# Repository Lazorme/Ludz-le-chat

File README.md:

# KittyLudzinator Project

## Project Overview
The KittyLudzinator Project is focused on developing a playful autonomous robot equipped with an array of sensors including IMUs, Lidar, and motion detectors. It engages in a game of TAG, showcasing its ability to navigate and interact within its environment.

CHARBONENAU TOM

SERVAN Antoine

GILLES Baptiste

## Table of Contents
- [Project Overview](#project-overview)
- [Installation](#installation)
- [Usage](#usage)
- [Robot Strategy](#robot-strategy)
- [Doxygen](#Doxygen)
- [IMU](#IMU)
- [Directory Structure](#directory-structure)
- [License](#license)
- [Acknowledgments](#acknowledgments)
- [Contact Information](#contact-information)

## Installation
Refer to the [PCB](/PCB) directory for detailed component tables , PCB info and setup documentation. The software setup is managed through STM32CubeMX configurations (`Ludz_le_chat.ioc`), 

## Usage
The source code is located in [Code_Chat_V4.0](/Code_Chat_V4.0) with core functions in [Core](/Code_Chat_V4.0/Core).

The Lidar and motor drivers are in [drv_LIDAR](/Code_Chat_V4.0/drv_LIDAR) and [drv_Motor](/Code_Chat_V4.0/drv_Motor), respectively.

## Robot Strategy
Strategies for robot behavior in different modes are implemented as follows:

### Lidar Processing
Processes Lidar sensor data to track objects. Details are in the script [LIDAR_Receive_clusters.py](/LIDAR_Receive_clusters.py).

### Mouse Mode
The robot moves away from the tagger, inversely proportional to the angle of the tagger's approach.

### Hunter Mode
The 'it' robot aggressively seeks the nearest robot, adjusting its motor speed using a linear function.

### Edge Sensor
Edge detection prevents the robot from falling off ledges.

## Doxygen

## IMU
[IIMU](<Autres Codes/Code_IIM2070_SPI>) :This file includes instructions for operating the IIM2070 device, as detailed in the script code 'IIM2070_SPI

## Directory Structure
- [Code_Chat_V4.0](/Code_Chat_V4.0): Active robot code.
- [PCB](/PCB): Documentation, components and manufacturing file for PCB.
- [Doxygen](/Doxygen): Generated code documentation.
- [Autres Codes](/Autres_Codes): Previous versions and experimental code.

## License
The project is under the MIT License.

## Acknowledgments
Thanks to contributors and the open-source community.

## Contact Information
Contact the maintainer at .
[tom.charbonneau2001@gmail.com](mailto:tom.charbonneau2001@gmail.com) | [baptiste.gilles01@gmail.com](mailto:baptiste.gilles01@gmail.com)   |  [servan.antoine@gmail.com](mailto:servan.antoine@gmail.com)

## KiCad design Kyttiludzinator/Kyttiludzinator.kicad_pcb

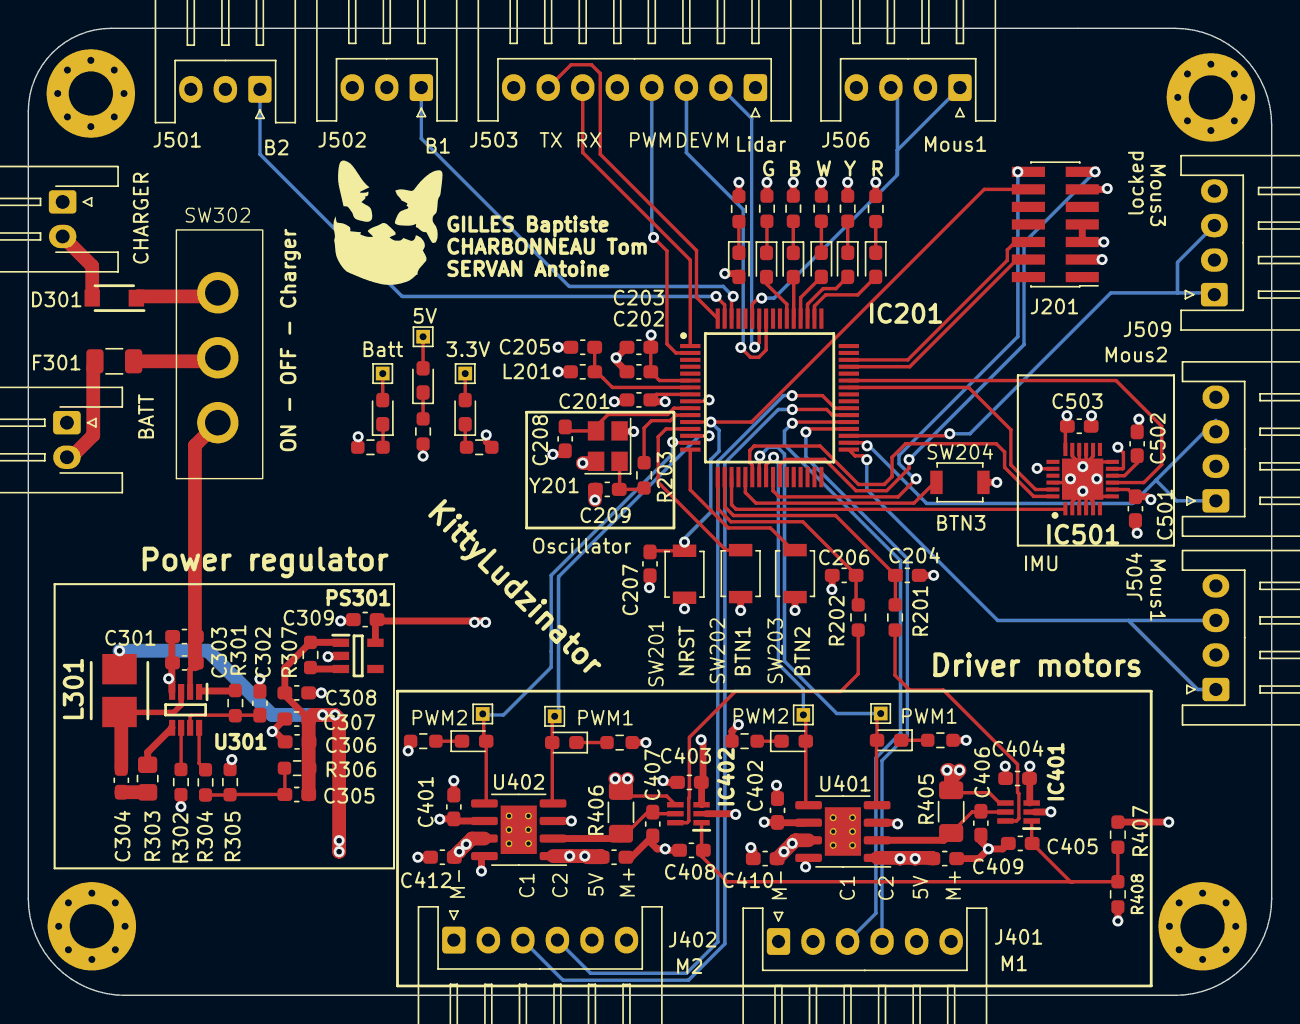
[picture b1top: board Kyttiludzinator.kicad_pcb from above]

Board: 4 copper layers, 90.0 x 70.0 mm, 104 parts (0 on the bottom side), 78 nets.

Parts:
Alim_batterie301: Conn_01x02; JST_XH_S2B-XH-A-1_1x02_P2.50mm_Horizontal
Alim_charger301: Conn_01x02; JST_XH_S2B-XH-A-1_1x02_P2.50mm_Horizontal
C201, C202, C205, C207, C403, C404, C405, C408, C502, C503: 100nF; C_0603_1608Metric_Pad1.08x0.95mm_HandSolder
C203: 4.7uF; C_0603_1608Metric_Pad1.08x0.95mm_HandSolder
C204, C206: 5pF; C_0603_1608Metric_Pad1.08x0.95mm_HandSolder
C208, C209: 10pF; C_0603_1608Metric_Pad1.08x0.95mm_HandSolder
C301, C306, C307: 22uF; C_0603_1608Metric_Pad1.08x0.95mm_HandSolder
C302, C303, C304: 0.1uF; C_0603_1608Metric_Pad1.08x0.95mm_HandSolder
C305: 15pF; C_0603_1608Metric_Pad1.08x0.95mm_HandSolder
C308, C309, C401, C402, C409, C410, C411, C412: 1uF; C_0603_1608Metric_Pad1.08x0.95mm_HandSolder
C406, C407: 10uF; C_0603_1608Metric_Pad1.08x0.95mm_HandSolder
C501: 10nF; C_0603_1608Metric_Pad1.08x0.95mm_HandSolder
D201: LED_ON; LED_0603_1608Metric_Pad1.05x0.95mm_HandSolder
D202, D401, D402, D403, D404, D404#2, D404#3, D404#4: RED; LED_0603_1608Metric_Pad1.05x0.95mm_HandSolder
D203: Yellow; LED_0603_1608Metric_Pad1.05x0.95mm_HandSolder
D204: BLUE; LED_0603_1608Metric_Pad1.05x0.95mm_HandSolder
D205: WHITE; LED_0603_1608Metric_Pad1.05x0.95mm_HandSolder
D206: GREEN; LED_0603_1608Metric_Pad1.05x0.95mm_HandSolder
D301: 1.5KExxA; SODFL3718X108N
F301: Polyfuse; Fuse_1206_3216Metric
IC201: STM32G070RBT6; QFP50P1200X1200X160-64N
IC401, IC402: NCS199A2RSQT2G; SOT65P210X110-6N
IC501: IIM-20670; IMU
J201: Conn_02x07_Odd_Even; PinHeader_2x07_P1.27mm_Vertical_SMD
J401, J402: Conn_01x06; JST_XH_S6B-XH-A_1x06_P2.50mm_Horizontal
J501, J502: Conn_01x03; JST_XH_S3B-XH-A_1x03_P2.50mm_Horizontal
J503: Conn_01x08; JST_XH_S8B-XH-A_1x08_P2.50mm_Horizontal
J504, J506, J509: Conn_01x04; JST_XH_S4B-XH-A_1x04_P2.50mm_Horizontal
L201: 6uH; L_0603_1608Metric_Pad1.05x0.95mm_HandSolder
L301: 4.7uH; INDPM4141X210N
PS301: MIC5317-3.3YM5-TR; SOT95P280X145-5N
R201, R202: 10k; R_0603_1608Metric_Pad0.98x0.95mm_HandSolder
R203: 10R; R_0603_1608Metric_Pad0.98x0.95mm_HandSolder
R204, R205, R206, R207, R208, R209: 3.3k; R_0603_1608Metric_Pad0.98x0.95mm_HandSolder
R301, R302, R307, R407, R408: 100k; R_0603_1608Metric_Pad0.98x0.95mm_HandSolder
R303: 20; R_0805_2012Metric_Pad1.20x1.40mm_HandSolder
R304: 16k; R_0603_1608Metric_Pad0.98x0.95mm_HandSolder
R305: 7.36k; R_0603_1608Metric_Pad0.98x0.95mm_HandSolder
R306: 40.2k; R_0603_1608Metric_Pad0.98x0.95mm_HandSolder
R401, R402, R403, R404#2: 390R; R_0603_1608Metric_Pad0.98x0.95mm_HandSolder
R404, R404#3, R404#4: 390; R_0603_1608Metric_Pad0.98x0.95mm_HandSolder
R405, R406: 0.015; R_1206_3216Metric_Pad1.30x1.75mm_HandSolder
REFe: MountingHole_3.2mm_M3_Pad_Via
SW201, SW202, SW203, SW204: SW_Push; SW_SPST_B3U-1000P
SW302: Switch; Switch-3
U301: MP1475DJ-LF-P; SOT65P280X100-8N
U401, U402: ZXBM5210-S; SOIC-8-1EP_3.9x4.9mm_P1.27mm_EP2.62x3.51mm_ThermalVias
Y201: 16MHz; Crystal_SMD_3225-4Pin_3.2x2.5mm
locked: Conn_01x04; JST_XH_S4B-XH-A_1x04_P2.50mm_Horizontal

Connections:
+3.3V: C201.1, C202.1, C203.1, C309.1, C403.1, C404.1, D201.2 (A), D404#3.2 (A), IC201.6 (VBAT), IC201.8 (VDD/VDDA), IC401.3 (VS), IC402.3 (VS), J201.3, J504.2, J504.4, J506.2, J506.4, J509.2, J509.4, L201.1, PS301.5 (VOUT), R404#4.2, R407.1, locked.2, locked.4
+5V: C305.2, C306.1, C307.1, C308.1, C401.1, C402.1, C501.2, C503.2, D404#4.2 (A), IC501.8 (VDDIO), IC501.11 (VDD), IC501.18 (RESETN), IC501.20 (VPP), J401.5, J402.5, J501.2, J502.2, J503.8, L301.2, PS301.1 (VIN), R306.2, R307.2, R404.1, U401.3 (VDD), U401.6 (VREF), U402.3 (VDD), U402.6 (VREF)
+BATT: C301.1, C303.1, D404.1 (K), D404.2 (A), IC402.4 (IN+), R302.2, R404#3.1, R405.1, R406.1, SW302.3 (C), U301.2 (IN)
/Drivers_moteurs/In_2-: C407.1, IC402.5 (IN-), R406.2, U402.2 (VM)
/Drivers_moteurs/M1_VM: C406.1, IC401.5 (IN-), R405.2, U401.2 (VM)
/Drivers_moteurs/Motor1+: C409.1, J401.6, U401.1 (OUT1)
/Drivers_moteurs/Motor1-: C410.1, J401.1, U401.7 (OUT2)
/Drivers_moteurs/Motor2+: C411.1, J402.6, U402.1 (OUT1)
/Drivers_moteurs/Motor2-: C412.1, J402.1, U402.7 (OUT2)
/Drivers_moteurs/REF: C405.1, C408.2, IC401.1 (REF), IC402.1 (REF), R407.2, R408.1
/STM32G070RBT6/BLUE: D204.2 (A), IC201.53 (PD3)
/STM32G070RBT6/BUTTON_1: IC201.13 (PC0), SW202.1
/STM32G070RBT6/BUTTON_2: IC201.16 (PC3), SW203.1
/STM32G070RBT6/BUTTON_3: IC201.21 (PA4), SW204.1
/STM32G070RBT6/GREEN: D206.2 (A), IC201.54 (PD4)
/STM32G070RBT6/NRST: C207.1, IC201.12 (NRST), J201.12, SW201.1
/STM32G070RBT6/OSC_IN: C208.1, IC201.10 (PF0-OSC_IN), Y201.3
/STM32G070RBT6/OSC_OUT: C209.2, IC201.11 (PF1-OSC_OUT), R203.1, R203.2, Y201.1
/STM32G070RBT6/RED: D202.2 (A), IC201.50 (PD0)
/STM32G070RBT6/RX: IC201.26 (PC5), J201.13
/STM32G070RBT6/SWCLK: IC201.46 (PA14-BOOT0), J201.6
/STM32G070RBT6/SWDIO: IC201.45 (PA13), J201.4
/STM32G070RBT6/TX: IC201.25 (PC4), J201.14
/STM32G070RBT6/VREF: C205.1, IC201.7 (VREF+), L201.2
/STM32G070RBT6/WHITE: D205.2 (A), IC201.52 (PD2)
/STM32G070RBT6/YELLOW: D203.2 (A), IC201.51 (PD1)
ADC_1: IC401.6 (OUT), R201.2
ADC_2: IC402.6 (OUT), R202.2
Bordure_1: IC201.62 (PB8), J502.1
Bordure_2: IC201.63 (PB9), J501.1
Codeur1_PH1: IC201.36 (PA8), J401.4
Codeur1_PH2: IC201.37 (PA9), J401.3
Codeur2_PH1: IC201.38 (PC6), J402.3
Codeur2_PH2: IC201.39 (PC7), J402.4
GND: Alim_batterie301.1, Alim_charger301.1, C201.2, C202.2, C203.2, C204.1, C205.2, C206.1, C207.2, C208.2, C209.1, C301.2, C302.1, C303.2, C306.2, C307.2, C308.2, C309.2, C401.2, C402.2, C403.2, C404.2, C405.2, C406.2, C407.2, C408.1, C409.2, C410.2, C411.2, C412.2, C501.1, C502.1, C503.1, IC201.9 (VSS/VSSA), IC401.2 (GND), IC402.2 (GND), IC501.2 (GND_1), IC501.3 (GND_2), IC501.4 (GND_3), IC501.5 (GND_4), IC501.7 (GND_5), IC501.12 (ODR), IC501.14 (GND_6), IC501.15 (GND_7), IC501.16 (GND_8), IC501.17 (GND_9), IC501.22 (GND_10), IC501.25 (THERMAL_PAD), J201.5, J201.7, J201.11, J401.2, J402.2, J501.3, J502.3, J503.5, PS301.2 (GND), R204.2, R205.2, R206.2, R207.2, R208.2, R209.2, R305.1, R401.2, R402.2, R403.2, R404.2, R404#2.2, R404#3.2, R404#4.1, R408.2, REFe.1, SW201.2, SW202.2, SW203.2, SW204.2, U301.4 (GND), U401.8 (GND), U402.8 (GND), Y201.2, Y201.4
LIDAR_DEV: IC201.57 (PB3), J503.3
LIDAR_M: IC201.58 (PB4), J503.2
LIDAR_PWM: IC201.2 (PC12), J503.4
LIDAR_RX: IC201.1 (PC11), J503.6
LIDAR_TX: IC201.64 (PC10), J503.7
Moustache_1: IC201.33 (PB13), J504.1, J504.3
Moustache_2: IC201.34 (PB14), J509.1, J509.3
Moustache_3: IC201.35 (PB15), locked.1, locked.3
Moustache_4: IC201.59 (PB5), J506.1, J506.3
unnamed: Alim_batterie301.2, F301.1
unnamed: Alim_charger301.2, D301.2 (A2)
unnamed: C304.2, R303.2
unnamed: C305.1, R304.2, R305.2, R306.1
unnamed: D201.1 (K), R204.1
unnamed: D202.1 (K), R205.1
unnamed: D203.1 (K), R206.1
unnamed: D204.1 (K), R207.1
unnamed: D205.1 (K), R208.1
unnamed: D206.1 (K), R209.1
unnamed: D301.1 (A1), SW302.1 (A)
unnamed: D401.1 (K), R401.1
unnamed: D402.1 (K), R402.1
unnamed: D403.1 (K), R403.1
unnamed: D404#2.1 (K), R404#2.1
unnamed: C206.2, IC201.17 (PA0), R202.1
unnamed: C204.2, IC201.18 (PA1), R201.1
unnamed: C502.2, IC501.10 (REGOUT)
unnamed: PS301.3 (EN), R307.1
unnamed: F301.2, SW302.2 (B)
unnamed: R303.1, U301.5 (BST)
unnamed: R302.1, U301.6 (EN/SYNC)
unnamed: R304.1, U301.8 (FB)
unnamed: R301.1, U301.1 (PG)
unnamed: C304.1, L301.1, U301.3 (SW)
unnamed: C302.2, R301.2, U301.7 (VCC)
PWM_MOT1_CH1: D401.2 (A), IC201.23 (PA6), U401.4 (FWD)
PWM_MOT1_CH2: D402.2 (A), IC201.24 (PA7), U401.5 (REV)
PWM_MOT2_CH1: D403.2 (A), IC201.14 (PC1), U402.4 (FWD)
PWM_MOT2_CH2: D404#2.2 (A), IC201.15 (PC2), U402.5 (REV)
SPI1_CS: IC201.42 (PA10), IC501.23 (NCS)
SPI1_MISO: IC201.43 (PA11_[PA9]), IC501.9 (MISO)
SPI1_MOSI: IC201.19 (PA2), IC501.1 (MOSI)
SPI1_SCK: IC201.22 (PA5), IC501.24 (SCLK)

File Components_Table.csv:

"Reference,""Value"",""Footprint"",""Datasheet"",""Height"",""Manufacturer_Name"",""Manufacturer_Part_Number"",""Mouser Part Number"",""Mouser Price/Stock"",""Qty"""
"Alim_batterie301,""Conn_01x02"",""Connector_JST:JST_XH_B2B-XH-A_1x02_P2.50mm_Vertical"",""~"","""","""","""","""","""",""1"""
"Alim_charger301,""Conn_01x02"",""Connector_JST:JST_XH_B2B-XH-A_1x02_P2.50mm_Vertical"",""~"","""","""","""","""","""",""1"""
"C201, C202, C205, C207, C403-C405, C502, C503,""100nF"",""Capacitor_SMD:C_0603_1608Metric_Pad1.08x0.95mm_HandSolder"",""~"","""","""","""","""","""",""9"""
"C203,""4.7uF"",""Capacitor_SMD:C_0603_1608Metric_Pad1.08x0.95mm_HandSolder"",""~"","""","""","""","""","""",""1"""
"C204, C206,""5pF"",""Capacitor_SMD:C_0603_1608Metric_Pad1.08x0.95mm_HandSolder"",""~"","""","""","""","""","""",""2"""
"C208, C209,""10pF"",""Capacitor_SMD:C_0603_1608Metric_Pad1.08x0.95mm_HandSolder"",""~"","""","""","""","""","""",""2"""
"C301, C306, C307,""22uF"",""Capacitor_SMD:C_0603_1608Metric_Pad1.08x0.95mm_HandSolder"",""~"","""","""","""","""","""",""3"""
"C302-C304,""0.1uF"",""Capacitor_SMD:C_0603_1608Metric_Pad1.08x0.95mm_HandSolder"",""~"","""","""","""","""","""",""3"""
"C305,""15pF"",""Capacitor_SMD:C_0603_1608Metric_Pad1.08x0.95mm_HandSolder"",""~"","""","""","""","""","""",""1"""
"C308, C309, C401, C402,""1uF"",""Capacitor_SMD:C_0603_1608Metric_Pad1.08x0.95mm_HandSolder"",""~"","""","""","""","""","""",""4"""
"C406, C407,""10uF"",""Capacitor_SMD:C_0603_1608Metric"",""~"","""","""","""","""","""",""2"""
"C501,""10nF"",""Capacitor_SMD:C_0603_1608Metric_Pad1.08x0.95mm_HandSolder"",""~"","""","""","""","""","""",""1"""
"D201,""LED_ON"",""LED_SMD:LED_0603_1608Metric_Pad1.05x0.95mm_HandSolder"",""~"","""","""","""","""","""",""1"""
"D202, D401-D404,""RED"",""LED_SMD:LED_0603_1608Metric_Pad1.05x0.95mm_HandSolder"",""~"","""","""","""","""","""",""5"""
"D203,""Yellow"",""LED_SMD:LED_0603_1608Metric_Pad1.05x0.95mm_HandSolder"",""~"","""","""","""","""","""",""1"""
"D204,""BLUE"",""LED_SMD:LED_0603_1608Metric_Pad1.05x0.95mm_HandSolder"",""~"","""","""","""","""","""",""1"""
"D205,""WHITE"",""LED_SMD:LED_0603_1608Metric_Pad1.05x0.95mm_HandSolder"",""~"","""","""","""","""","""",""1"""
"D206,""GREEN"",""LED_SMD:LED_0603_1608Metric_Pad1.05x0.95mm_HandSolder"",""~"","""","""","""","""","""",""1"""
"D301,""1.5KExxA"",""Library:SODFL3718X108N"",""https://www.vishay.com/docs/88301/15ke.pdf"","""",""Vishay"","""","" 78-SS2FN6HM3/H "",""https://www.mouser.fr/ProductDetail/Vishay-General-Semicondu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"",""1"""
"F301,""Polyfuse"",""Fuse:Fuse_1206_3216Metric"",""~https://www.mouser.fr/datasheet/2/54/bourns_01242019_MF-NSML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"",""1206"",""Boums"","""","" 652-MF-NSML150/12-2 "",""https://www.mouser.fr/ProductDetail/Bourns/MF-NSML150-12-2?q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"",""1"""
"IC201,""STM32G070RBT6"",""Library:QFP50P1200X1200X160-64N"",""https://componentsearchengine.com/Datasheets/1/STM32G070RBT6.pdf"",""1.6"",""STMicroelectronics"",""STM32G070RBT6 "",""511-STM32G070RBT6"",""https://www.mouser.co.uk/ProductDetail/STMicroelectronics/ST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"",""1"""
"IC401, IC402,""NCS199A2RSQT2G"",""Library:SOT65P210X110-6N"",""http://www.onsemi.com/pub/Collateral/NCS199A1R-D.PDF"",""1.1"",""onsemi"",""NCS199A2RSQT2G"",""863-NCS199A2RSQT2G"",""https://www.mouser.co.uk/ProductDetail/onsemi/NCS199A2RSQT2G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"",""2"""
"IC501,""IIM-20670"",""Library:IMU"",""https://invensense.tdk.com/download-pdf/iim-20670-product-brief/"",""1.15"",""TDK"",""IIM-20670"","" 410-IIM-20670 "",""https://www.mouser.fr/ProductDetail/TDK-InvenSense/IIM-20670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"",""1"""
"J201,""Conn_02x07_Odd_Even"",""Connector_PinHeader_2.54mm:PinHeader_2x07_P2.54mm_Vertical"",""~"","""","""","""","""","""",""1"""
"J401, J402,""Conn_01x06"",""Connector_JST:JST_XH_B6B-XH-A_1x06_P2.50mm_Vertical"",""~"","""","""","""","""","""",""2"""
"J501, J502, J504-J507,""Conn_01x03"",""Connector_JST:JST_XH_B3B-XH-A_1x03_P2.50mm_Vertical"",""~"","""","""","""","""","""",""6"""
"J503,""Conn_01x08"",""Connector_JST:JST_XH_B8B-XH-A_1x08_P2.50mm_Vertical"",""~"","""","""","""","""","""",""1"""
"L201,""6uH"",""Inductor_SMD:L_0603_1608Metric"",""~"","""","""","""","""","""",""1"""
"L301,""4.7uH"",""Library:INDPM4141X210N"",""https://www.we-online.com/components/products/datasheet/7443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"","""",""Wurth"",""74438356047HT "","" 710-74438356047HT "",""https://www.mouser.fr/ProductDetail/Wurth-Elektronik/7443835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"",""1"""
"PS301,""MIC5317-3.3YM5-TR"",""Library:SOT95P280X145-5N"",""http://ww1.microchip.com/downloads/en/devicedoc/mic5317.pdf"",""1.45"",""Microchip"",""MIC5317-3.3YM5-TR"",""998-MIC5317-3.3YM5TR"",""https://www.mouser.co.uk/ProductDetail/Microchip-Technology/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"",""1"""
"R201, R202,""10k"",""Resistor_SMD:R_0603_1608Metric_Pad0.98x0.95mm_HandSolder"",""~"",""0603"","""","""","""","""",""2"""
"R203,""10R"",""Resistor_SMD:R_0603_1608Metric_Pad0.98x0.95mm_HandSolder"",""~"",""0603"","""","""","""","""",""1"""
"R204-R209,""3.3k"",""Resistor_SMD:R_0603_1608Metric_Pad0.98x0.95mm_HandSolder"",""~"",""0603"","""","""","""","""",""6"""
"R301, R302, R407, R408,""100k"",""Resistor_SMD:R_0603_1608Metric_Pad0.98x0.95mm_HandSolder"",""~"",""0603"","""","""","""","""",""4"""
"R303,""20"",""Resistor_SMD:R_0805_2012Metric_Pad1.20x1.40mm_HandSolder"",""~"",""0805"","""","""","""","""",""1"""
"R304,""16k"",""Resistor_SMD:R_0603_1608Metric_Pad0.98x0.95mm_HandSolder"",""~"",""0603"","""","""","""","""",""1"""
"R305,""7.36k"",""Resistor_SMD:R_0603_1608Metric_Pad0.98x0.95mm_HandSolder"",""~"",""0603"","""","""","""","""",""1"""
"R306,""40.2k"",""Resistor_SMD:R_0603_1608Metric_Pad0.98x0.95mm_HandSolder"",""~"",""0603"","""","""","""","""",""1"""
"R401-R404,""390R"",""Resistor_SMD:R_0603_1608Metric_Pad0.98x0.95mm_HandSolder"",""~"",""0603"","""","""","""","""",""4"""
"R405, R406,""0.015"",""Resistor_SMD:R_1206_3216Metric_Pad1.30x1.75mm_HandSolder"",""~"",""0603"","""","""","""","""",""2"""
"SW201-SW204,""SW_Push"",""Button_Switch_SMD:SW_SPST_B3U-1000P"",""~"",""1206"","""","""","""","""",""4"""
"SW302,""Switch"",""Library:Switch-3"",""https://www.we-online.com/en/components/products/WS-TOTV_635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"","""",""Wurth"",""WS-TOTV Ø 6.35mm"",""1333652"","""",""1"""
"U301,""MP1475DJ-LF-P"",""Library:SOT65P280X100-8N"",""https://www.mouser.fr/datasheet/2/277/MP1475-2945395.pdf"","""","" Monolithic Power Systems (MPS)"",""MP1475DJ"","" 946-MP1475DJLFP "",""https://www.mouser.fr/ProductDetail/Monolithic-Power-Systems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"",""1"""
"U401, U402,""ZXBM5210-S"",""Library:SOIC127P600X175-8N"",""https://www.diodes.com/assets/Datasheets/ZXBM5210.pdf"","""","""","""","" 621-ZXBM5210-SP-13 "",""https://www.mouser.fr/ProductDetail/Diodes-Incorporated/ZXBM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"",""2"""
"Y201,""16MHz"",""Crystal:Crystal_SMD_3225-4Pin_3.2x2.5mm"",""https://www.farnell.com/datasheets/3820205.pdf"","""",""ZXBM5210-SP-13"",""Diodes Incorporated "",""2853935"","""",""1"""

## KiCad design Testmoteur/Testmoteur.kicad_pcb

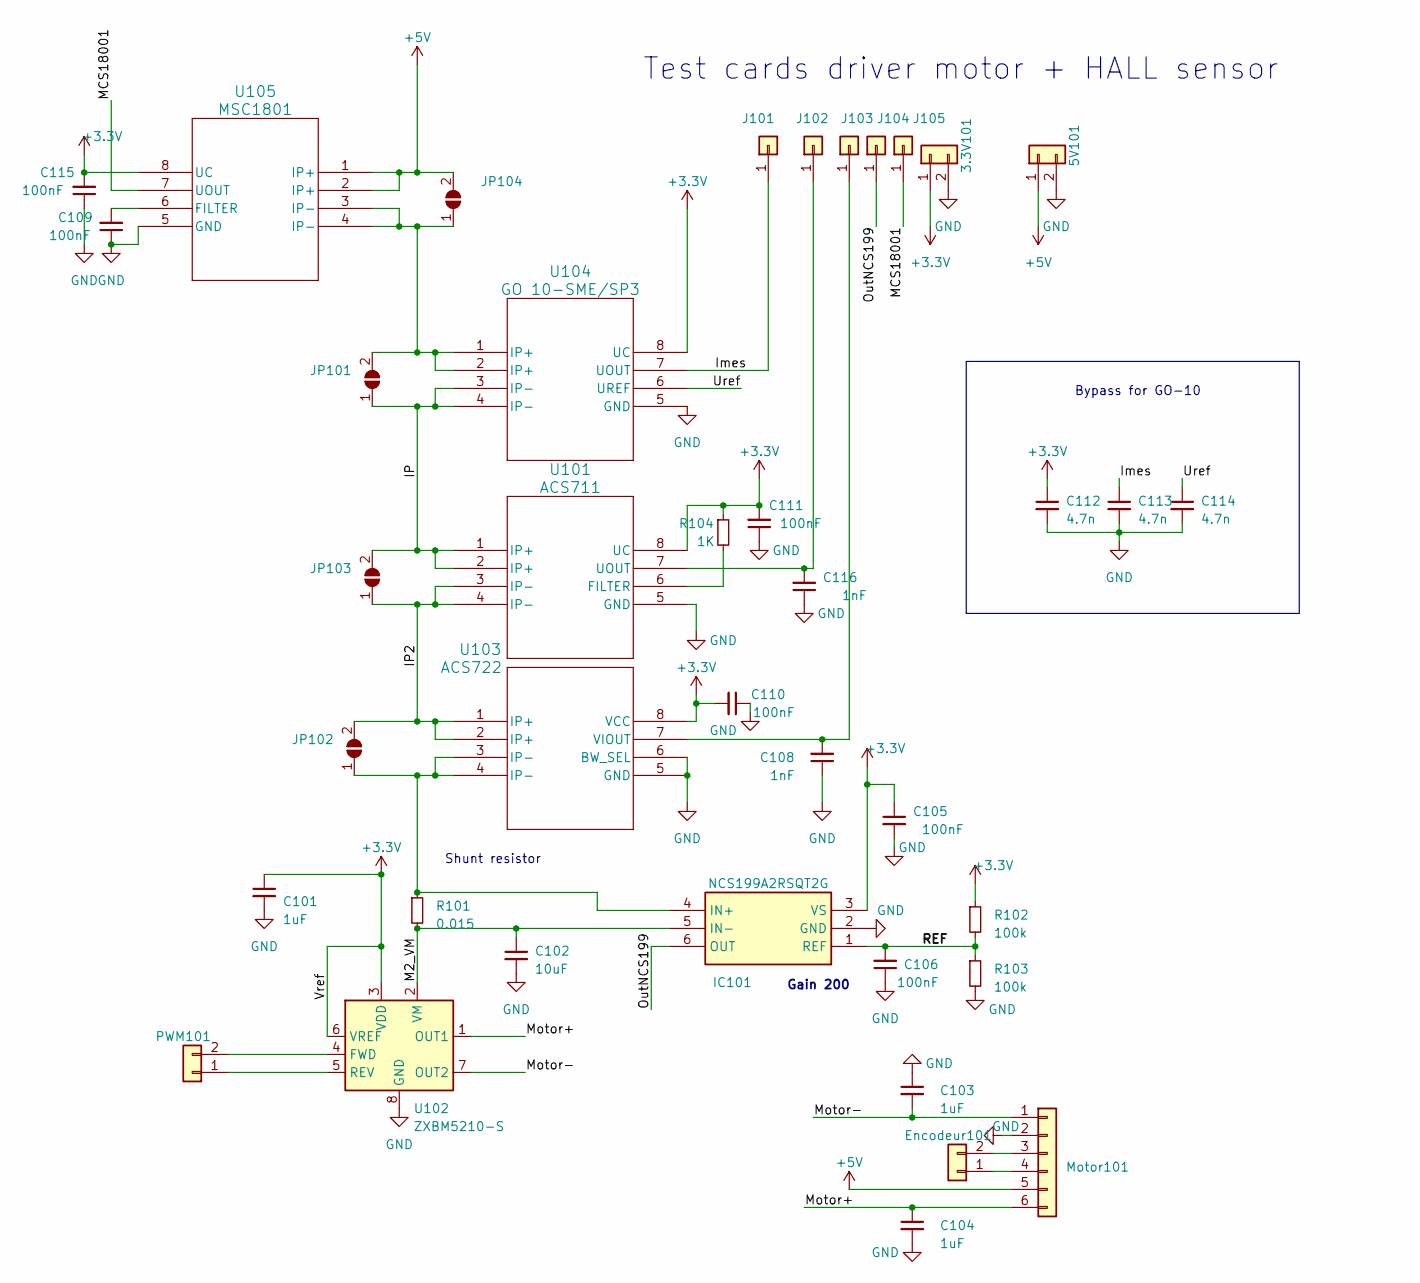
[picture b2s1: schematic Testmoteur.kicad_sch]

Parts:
3.3V101, 5V101: Conn_01x02; PinSocket_1x02_P2.54mm_Vertical
C101, C103, C104: 1uF; C_0603_1608Metric_Pad1.08x0.95mm_HandSolder
C102: 10uF; C_0603_1608Metric
C105, C106, C109, C110, C111, C115: 100nF; C_0603_1608Metric_Pad1.08x0.95mm_HandSolder
C108, C116: 1nF; C_0603_1608Metric_Pad1.08x0.95mm_HandSolder
C112, C113, C114: 4.7n; C_0603_1608Metric_Pad1.08x0.95mm_HandSolder
Encodeur101: Conn_01x02; PinSocket_1x02_P2.54mm_Vertical
IC101: NCS199A2RSQT2G; SOT65P210X110-6N; Mouser Part Number 863-NCS199A2RSQT2G
J101, J102, J103, J104, J105: Conn_01x01; PinSocket_1x01_P2.00mm_Vertical
JP101, JP102, JP103, JP104: SolderJumper_2_Open; SolderJumper-2_P1.3mm_Open_TrianglePad1.0x1.5mm
Motor101: Conn_01x06; PinSocket_1x06_P2.54mm_Vertical
PWM101: Conn_01x02; PinSocket_1x02_P2.54mm_Vertical
R101: 0.015; R_1206_3216Metric_Pad1.30x1.75mm_HandSolder
R102, R103: 100k; R_0603_1608Metric_Pad0.98x0.95mm_HandSolder
R104: 1K; R_0603_1608Metric_Pad0.98x0.95mm_HandSolder
U101: ACS711; SOIC127P600X175-8N
U102: ZXBM5210-S; SOIC127P600X175-8N; Mouser Part Number 621-ZXBM5210-SP-13
U103: ACS722; SOIC127P600X175-8N
U104: GO 10-SME/SP3; SOIC8-GO-SME&slash_SP3_LEM
U105: MSC1801; SOIC127P600X175-8N

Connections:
+3.3V: 3.3V101.1, C101.1, C105.1, C110.2, C111.2, C112.1, C115.2, IC101.3 (VS), R102.1, R104.1, U101.8 (UC), U102.3 (VDD), U102.6 (VREF), U103.8 (VCC), U104.8 (UC), U105.8 (UC)
+5V: 5V101.1, JP104.2 (B), Motor101.5, U105.1 (IP+), U105.2 (IP+)
/IP: JP101.1 (A), JP103.2 (B), U101.1 (IP+), U101.2 (IP+), U104.3 (IP-), U104.4 (IP-)
/IP2: JP102.2 (B), JP103.1 (A), U101.3 (IP-), U101.4 (IP-), U103.1 (IP+), U103.2 (IP+)
/Imes: C113.1, J101.1, U104.7 (UOUT)
/M2_VM: C102.1, IC101.5 (IN-), R101.2, U102.2 (VM)
/MCS18001: J105.1, U105.7 (UOUT)
/Motor+: C104.1, Motor101.6, U102.1 (OUT1)
/Motor-: C103.2, Motor101.1, U102.7 (OUT2)
/OutNCS199: IC101.6 (OUT), J104.1
/REF: C106.2, IC101.1 (REF), R102.2, R103.1
/Uref: C114.1, U104.6 (UREF)
GND: 3.3V101.2, 5V101.2, C101.2, C102.2, C103.1, C104.2, C105.2, C106.1, C108.1, C109.1, C110.1, C111.1, C112.2, C113.2, C114.2, C115.1, C116.1, IC101.2 (GND), Motor101.2, R103.2, U101.5 (GND), U102.8 (GND), U103.5 (GND), U103.6 (BW_SEL), U104.5 (GND), U105.5 (GND); also elsewhere on the board
unnamed: Encodeur101.1, Motor101.4
unnamed: Encodeur101.2, Motor101.3
unnamed: IC101.4 (IN+), JP102.1 (A), R101.1, U103.3 (IP-), U103.4 (IP-)
unnamed: C116.2, J102.1, U101.7 (UOUT)
unnamed: C108.2, J103.1, U103.7 (VIOUT)
unnamed: JP101.2 (B), JP104.1 (A), U104.1 (IP+), U104.2 (IP+), U105.3 (IP-), U105.4 (IP-)
unnamed: PWM101.1, U102.5 (REV)
unnamed: PWM101.2, U102.4 (FWD)
unnamed 21: R104.2, U101.6 (FILTER); also elsewhere on the board
unnamed: C109.2, U105.6 (FILTER)

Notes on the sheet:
Test cards driver motor + HALL sensor
Gain 200
Shunt resistor
Bypass for GO-10

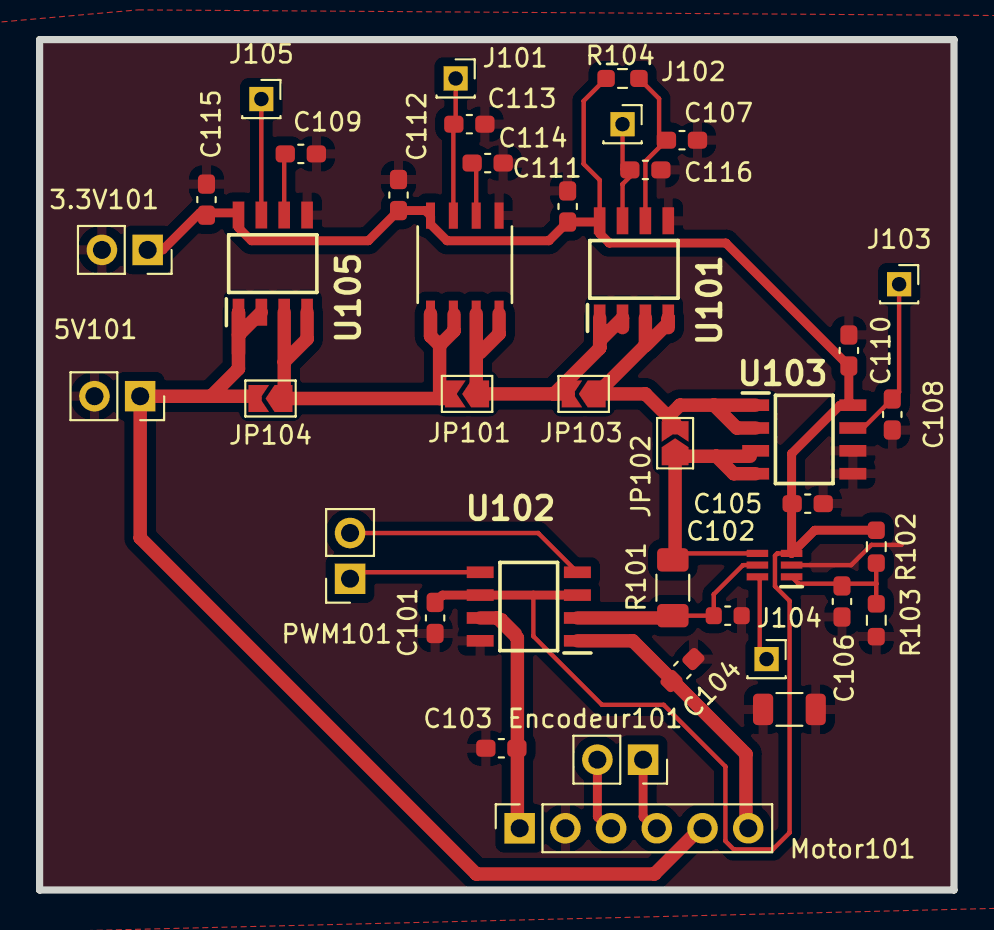
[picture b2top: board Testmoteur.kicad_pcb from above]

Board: 2 copper layers, 50.8 x 47.2 mm, 41 parts (0 on the bottom side), 23 nets.

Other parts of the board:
C107: 100nF; C_0603_1608Metric_Pad1.08x0.95mm_HandSolder
GND: R_1206_3216Metric

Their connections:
GND: C107.1, GND.1, GND.GND; also elsewhere on the board
unnamed 21: C107.2; also elsewhere on the board

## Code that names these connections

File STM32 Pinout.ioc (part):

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Mcu.Name=STM32G070RBTx
Mcu.Package=LQFP64
Mcu.UserName=STM32G070RBTx
PA0.GPIOParameters=GPIO_Label
PA0.GPIO_Label=ADC_Shunt1
PA0.Mode=IN0
PA0.Signal=ADC1_IN0
PA1.GPIOParameters=GPIO_Label
PA1.GPIO_Label=ADC_Shunt2
PA1.Mode=IN1
PA1.Signal=ADC1_IN1
PA10.GPIOParameters=GPIO_Label
PA10.GPIO_Label=SPI1_CS
PA10.Signal=GPIO_Output
PA11\ [PA9].Mode=Full_Duplex_Master
PA11\ [PA9].Signal=SPI1_MISO
PA13.Mode=Serial_Wire
PA13.Signal=SYS_SWDIO
PA14-BOOT0.Mode=Serial_Wire
PA14-BOOT0.Signal=SYS_SWCLK
PA2.Mode=Full_Duplex_Master
PA2.Signal=SPI1_MOSI
PA4.GPIOParameters=GPIO_PuPd,GPIO_Label
PA4.GPIO_Label=Bouton3
PA4.GPIO_PuPd=GPIO_NOPULL
PA4.Signal=GPXTI4
PA5.Mode=Full_Duplex_Master
PA5.Signal=SPI1_SCK
PA6.GPIOParameters=GPIO_Label
PA6.GPIO_Label=PWM_MOT1_PH1
PA6.Signal=S_TIM16_CH1
PA7.GPIOParameters=GPIO_Label
PA7.GPIO_Label=PWM_MOT1_PH2
PA7.Signal=S_TIM17_CH1
PA8.GPIOParameters=GPIO_Label
PA8.GPIO_Label=CODEUR1_PH1
PA8.Signal=S_TIM1_CH1
PA9.GPIOParameters=GPIO_Label
PA9.GPIO_Label=CODEUR1_PH2
PA9.Signal=S_TIM1_CH2
PB13.GPIOParameters=GPIO_PuPd,GPIO_Label
PB13.GPIO_Label=Contact1
PB13.GPIO_PuPd=GPIO_PULLDOWN
PB13.Signal=GPXTI13
PB14.GPIOParameters=GPIO_PuPd,GPIO_Label
PB14.GPIO_Label=Contact2
PB14.GPIO_PuPd=GPIO_PULLDOWN
PB14.Signal=GPXTI14
PB15.GPIOParameters=GPIO_PuPd,GPIO_Label
PB15.GPIO_Label=Contact3
PB15.GPIO_PuPd=GPIO_PULLDOWN
PB15.Signal=GPXTI15
PB3.GPIOParameters=GPIO_Label
PB3.GPIO_Label=DEV_EN
PB3.Signal=GPIO_Output
PB4.GPIOParameters=GPIO_Label
PB4.GPIO_Label=M_EN
PB4.Signal=GPIO_Output
PB5.GPIOParameters=GPIO_PuPd,GPIO_Label
PB5.GPIO_Label=Contact4
PB5.GPIO_PuPd=GPIO_PULLDOWN
PB5.Signal=GPXTI5
PB8.GPIOParameters=GPIO_Label
PB8.GPIO_Label=Bordure1
PB8.Signal=GPXTI8
PB9.GPIOParameters=GPIO_Label
PB9.GPIO_Label=Bordure2
PB9.Signal=GPXTI9
PC0.GPIOParameters=GPIO_Label
PC0.GPIO_Label=Bouton1
PC0.Signal=GPXTI0
PC1.GPIOParameters=GPIO_Label
PC1.GPIO_Label=PWM_MOT2_PH1
PC1.Signal=S_TIM15_CH1
PC10.GPIOParameters=GPIO_Label
PC10.GPIO_Label=USART4_TX_LIDAR
PC10.Mode=Asynchronous
PC10.Signal=USART4_TX
PC11.GPIOParameters=GPIO_Label
PC11.GPIO_Label=USART4_RX_LIDAR
PC11.Mode=Asynchronous
PC11.Signal=USART4_RX
PC12.GPIOParameters=GPIO_Label
PC12.GPIO_Label=PWM_MOT_LIDAR
PC12.Signal=S_TIM14_CH1
PC2.GPIOParameters=GPIO_Label
PC2.GPIO_Label=PWM_MOT2_PH2
PC2.Signal=S_TIM15_CH2
PC3.GPIOParameters=GPIO_Label
PC3.GPIO_Label=Bouton2
PC3.Signal=GPXTI3
PC4.GPIOParameters=GPIO_Label
PC4.GPIO_Label=USART1_TX_Debug
PC4.Mode=Asynchronous
PC4.Signal=USART1_TX
PC5.GPIOParameters=GPIO_Label
PC5.GPIO_Label=USART1_RX_Debug
PC5.Mode=Asynchronous
PC5.Signal=USART1_RX
PC6.GPIOParameters=GPIO_Label
PC6.GPIO_Label=CODEUR2_PH1
PC6.Signal=S_TIM3_CH1
PC7.GPIOParameters=GPIO_Label
PC7.GPIO_Label=CODEUR2_PH2
PC7.Signal=S_TIM3_CH2
PD0.GPIOParameters=GPIO_Label
PD0.GPIO_Label=LED_RED
PD0.Signal=GPIO_Output
PD1.GPIOParameters=GPIO_Label
PD1.GPIO_Label=LED_YELLOW
PD1.Signal=GPIO_Output
PD2.GPIOParameters=GPIO_Label
PD2.GPIO_Label=LED_WHITE
PD2.Signal=GPIO_Output
PD3.GPIOParameters=GPIO_Label
PD3.GPIO_Label=LED_BLUE
PD3.Signal=GPIO_Output
PD4.GPIOParameters=GPIO_Label
PD4.GPIO_Label=LED_GREEN
PD4.Signal=GPIO_Output
PD5.GPIOParameters=GPIO_Label
PD5.GPIO_Label=Buzzer
PD5.Signal=GPIO_Output
PF0-OSC_IN\ (PF0).Mode=HSE-External-Oscillator
PF0-OSC_IN\ (PF0).Signal=RCC_OSC_IN
PF1-OSC_OUT\ (PF1).Mode=HSE-External-Oscillator
PF1-OSC_OUT\ (PF1).Signal=RCC_OSC_OUT
RCC.HSE_VALUE=16000000
RCC.SYSCLKFreq_VALUE=64000000
RCC.SYSCLKSource=RCC_SYSCLKSOURCE_PLLCLK
board=custom

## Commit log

2023-09-21 Add files via upload
    Le pinout du STM32
2023-09-21 version Antoine 21-09-23
2023-09-21 Ajout du lien d'une video sur le lidar
2023-09-21 Modification de l'ioc pour rajouter le SPI
2023-09-21 Update ioc
2023-10-05 MAJ KIKAD
2023-10-05 Ajout du logo beluga
2023-10-05 MAJ LOGO
2023-10-05 modif connecteur
2023-10-12 Moteur
2023-10-26 Finalversion
2024-01-08 Fresion final du code freertos
2024-01-11 Ajout des différents codes à différentes avancées
2024-01-12 Ajout des bordures et des contactes
2024-01-13 last code
2024-01-14 modifs des variables
2024-01-16 Ajout du doxygen
2024-01-17 final
